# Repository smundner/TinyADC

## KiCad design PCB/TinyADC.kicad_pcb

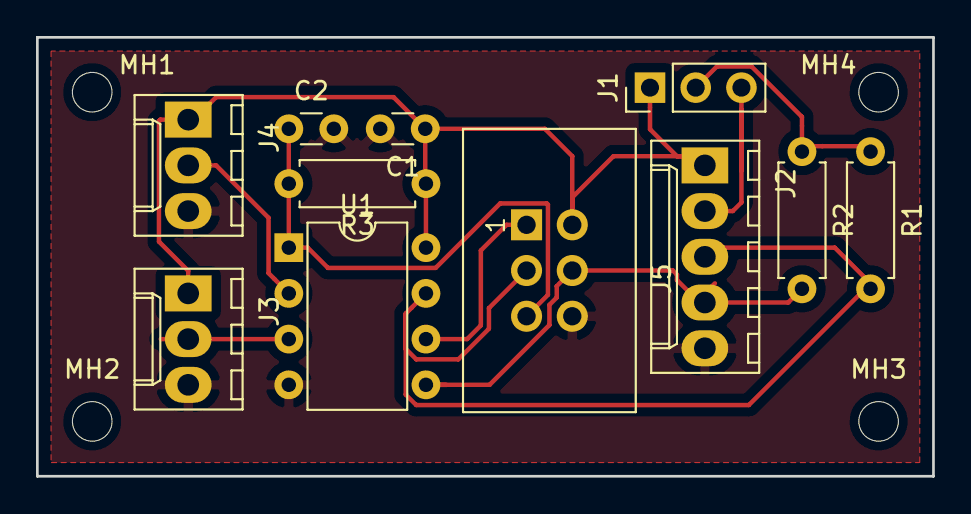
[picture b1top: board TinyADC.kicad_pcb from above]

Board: 2 copper layers, 49.8 x 24.4 mm, 15 parts (0 on the bottom side), 10 nets.

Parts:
C1, C2: C; C_Disc_D3.0mm_W1.6mm_P2.50mm
J1: Conn_01x03; PinHeader_1x03_P2.54mm_Vertical
J2: Conn_01x05; Molex_KK-6410-05_05x2.54mm_Straight
J3, J4: Conn_01x03; Molex_KK-6410-03_03x2.54mm_Straight
J5: Conn_02x03_Odd_Even; IDC_Header_Straight_6pins
MH1, MH2, MH3, MH4: MountingHole; MountingHole_2.2mm_M2_DIN965
R1, R2, R3: R; R_Axial_DIN0207_L6.3mm_D2.5mm_P7.62mm_Horizontal
U1: ATtiny85-20PU; DIP-8_W7.62mm

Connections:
+3V3: J1.3, J2.2
/ADC2: J3.2, U1.3
/ADC3: J4.2, U1.2
/MISO: J5.1, U1.6
/RESET: C2.1, J5.5, R3.2, U1.1
/SCL: J2.3, J5.3, R1.2, U1.7
/SDA: J2.4, J5.4, R2.2, U1.5
GND: C1.2, C2.2, J2.5, J3.3, J4.3, J5.6, U1.4
unnamed: J1.2, R1.1, R2.1
VCC: C1.1, J1.1, J2.1, J3.1, J4.1, J5.2, R3.1, U1.8

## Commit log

2020-01-29 position stecker geändert
